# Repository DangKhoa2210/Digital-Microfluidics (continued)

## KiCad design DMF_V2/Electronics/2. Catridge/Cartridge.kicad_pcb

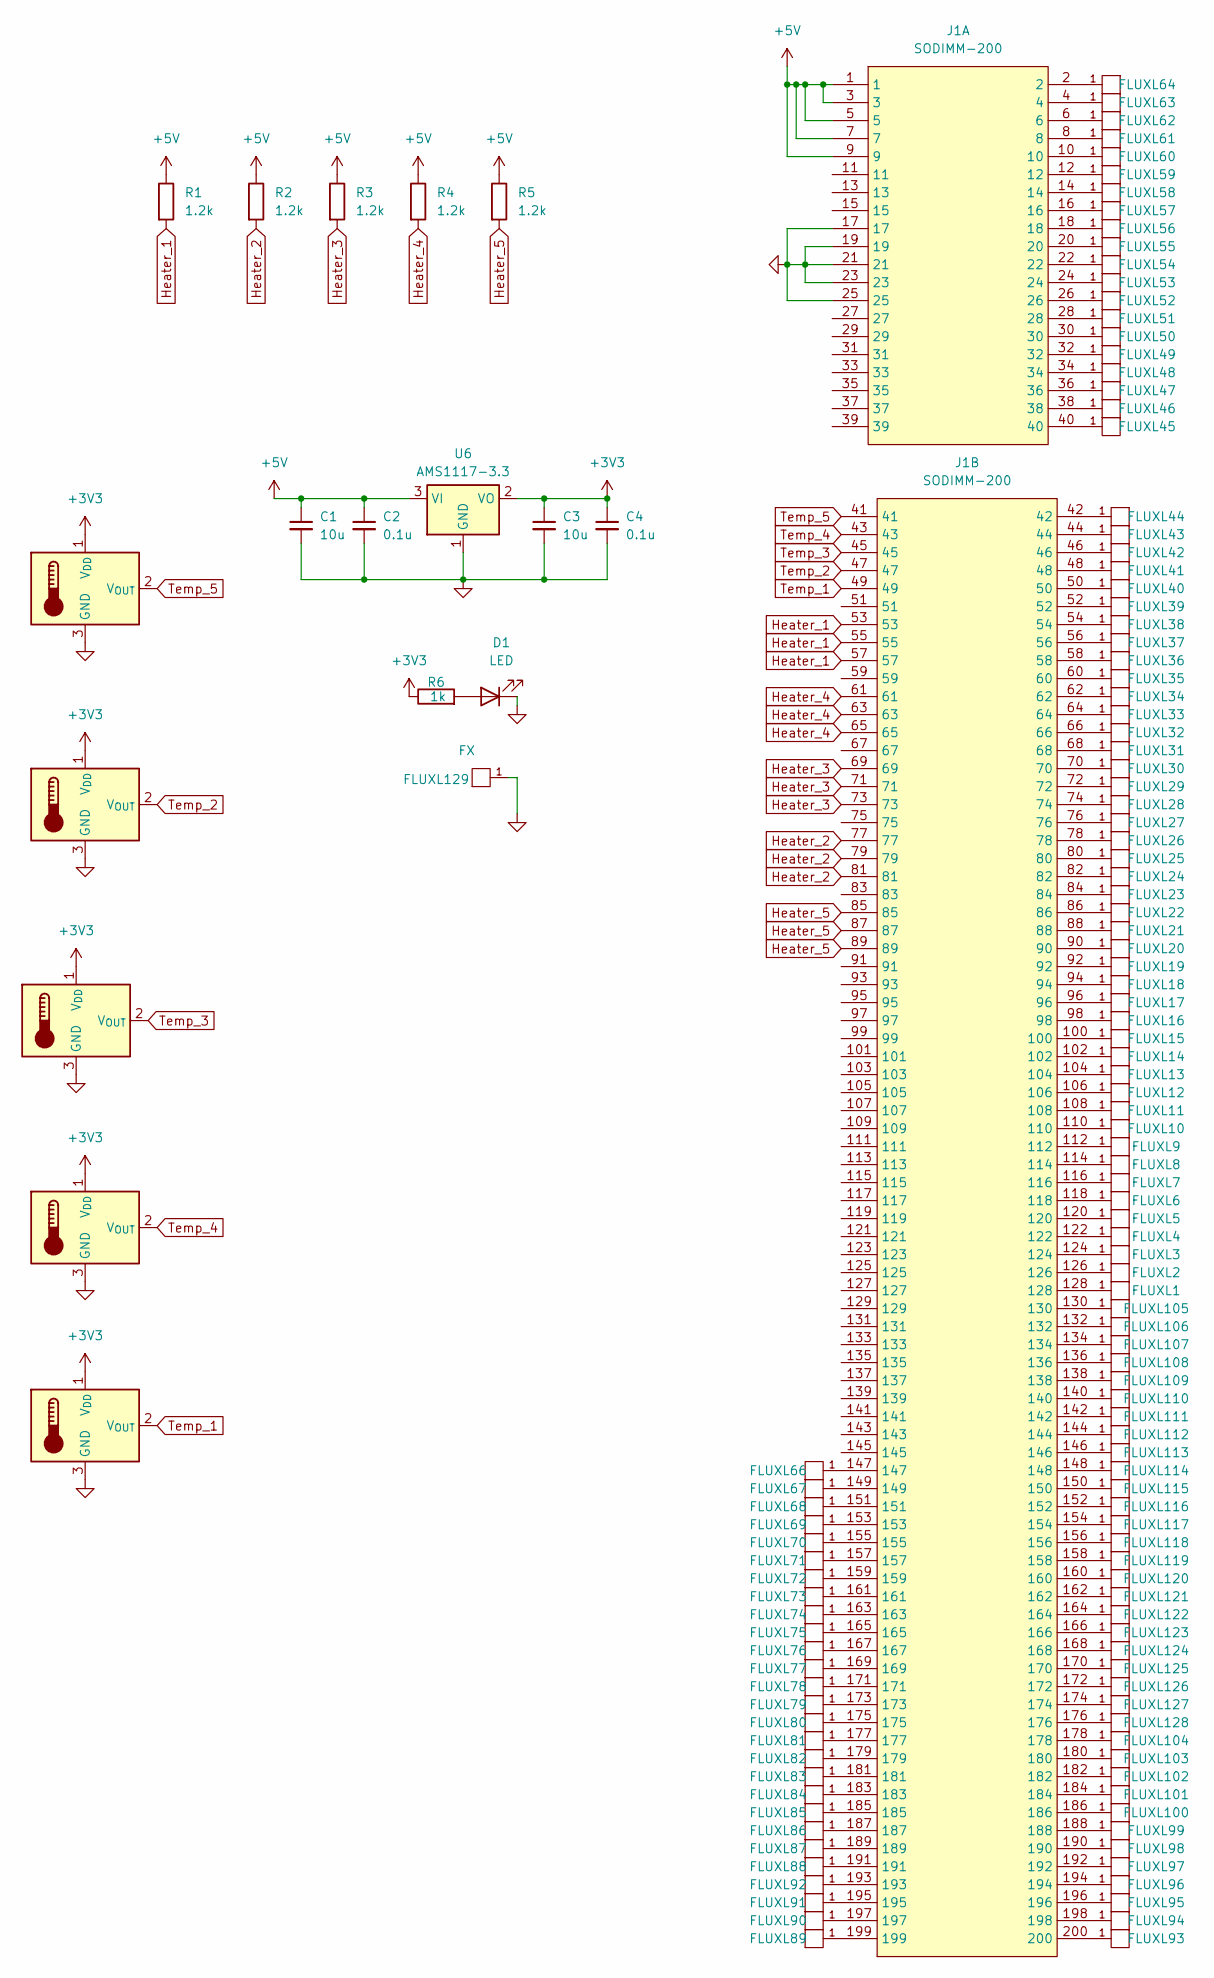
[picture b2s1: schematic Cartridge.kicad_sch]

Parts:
C1, C3: 10u; C_0402_1005Metric
C2, C4: 0.1u; C_0402_1005Metric
D1: LED; LED_0603_1608Metric
FLUXL1, FLUXL2, FLUXL3, FLUXL4, FLUXL5, FLUXL6, FLUXL7, FLUXL8, FLUXL9, FLUXL10, FLUXL11, FLUXL12, FLUXL13, FLUXL14, FLUXL15, FLUXL16, FLUXL17, FLUXL18, FLUXL19, FLUXL20, FLUXL21, FLUXL22, FLUXL23, FLUXL24, FLUXL25, FLUXL26, FLUXL27, FLUXL28, FLUXL29, FLUXL30, FLUXL31, FLUXL32, FLUXL33, FLUXL34, FLUXL35, FLUXL36, FLUXL37, FLUXL38, FLUXL39, FLUXL40, FLUXL41, FLUXL42, FLUXL43, FLUXL44, FLUXL45, FLUXL46, FLUXL47, FLUXL48, FLUXL49, FLUXL50, FLUXL51, FLUXL52, FLUXL53, FLUXL54, FLUXL55, FLUXL56, FLUXL57, FLUXL58, FLUXL59, FLUXL60, FLUXL61, FLUXL66, FLUXL67, FLUXL68, FLUXL69, FLUXL70, FLUXL71, FLUXL72, FLUXL73, FLUXL74, FLUXL75, FLUXL76, FLUXL77, FLUXL78, FLUXL79, FLUXL80, FLUXL81, FLUXL82, FLUXL83, FLUXL84, FLUXL85, FLUXL86, FLUXL87, FLUXL88, FLUXL89, FLUXL90, FLUXL91, FLUXL92, FLUXL93, FLUXL94, FLUXL95, FLUXL96, FLUXL97, FLUXL98, FLUXL99, FLUXL100, FLUXL101, FLUXL102, FLUXL103, FLUXL104, FLUXL105, FLUXL106, FLUXL107, FLUXL108, FLUXL109, FLUXL110, FLUXL111, FLUXL112, FLUXL113, FLUXL114, FLUXL115, FLUXL116, FLUXL117, FLUXL118, FLUXL119, FLUXL120, FLUXL121, FLUXL122, FLUXL123, FLUXL124, FLUXL125, FLUXL126, FLUXL127, FLUXL128: FX; FLUXPAD_2_75_4MIL_4_5
FLUXL62: FX; FLUXPAD_2_75_4MIL_4_5_res1
FLUXL63: FX; FLUXPAD_2_75_4MIL_4_5_res2
FLUXL64: FX; FLUXPAD_2_75_4MIL_4_5_res3
FLUXL129: FX; Pad_4mm_10mm
J1: SODIMM-200; DDR2
R1, R2, R3, R4, R5: 1.2k; R_1206_3216Metric
R6: 1k; R_0402_1005Metric
U1, U2, U3, U4, U5: MCP9700Ax-ETT; SOT-23
U6: AMS1117-3.3; SOT-223-3_TabPin2

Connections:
+3V3: C3.1, C4.1, R6.1, U1.1 (V_{DD}), U2.1 (V_{DD}), U3.1 (V_{DD}), U4.1 (V_{DD}), U5.1 (V_{DD}), U6.2 (VO)
+5V: C1.1, C2.1, J1.1, J1.3, J1.5, J1.7, J1.9, R1.1, R2.1, R3.1, R4.1, R5.1, U6.3 (VI)
GND: C1.2, C2.2, C3.2, C4.2, D1.1 (K), FLUXL129.1, J1.17, J1.19, J1.21, J1.23, J1.25, U1.3 (GND), U2.3 (GND), U3.3 (GND), U4.3 (GND), U5.3 (GND), U6.1 (GND)
Heater_1: J1.53, J1.55, J1.57, R1.2
Heater_2: J1.77, J1.79, J1.81, R2.2
Heater_3: J1.69, J1.71, J1.73, R3.2
Heater_4: J1.61, J1.63, J1.65, R4.2
Heater_5: J1.85, J1.87, J1.89, R5.2
unnamed: D1.2 (A), R6.2
unnamed: FLUXL1.1, J1.128
unnamed: FLUXL2.1, J1.126
unnamed: FLUXL3.1, J1.124
unnamed: FLUXL4.1, J1.122
unnamed: FLUXL5.1, J1.120
unnamed: FLUXL6.1, J1.118
unnamed: FLUXL7.1, J1.116
unnamed: FLUXL8.1, J1.114
unnamed: FLUXL9.1, J1.112
unnamed: FLUXL10.1, J1.110
unnamed: FLUXL11.1, J1.108
unnamed: FLUXL12.1, J1.106
unnamed: FLUXL13.1, J1.104
unnamed: FLUXL14.1, J1.102
unnamed: FLUXL15.1, J1.100
unnamed: FLUXL16.1, J1.98
unnamed: FLUXL17.1, J1.96
unnamed: FLUXL18.1, J1.94
unnamed: FLUXL19.1, J1.92
unnamed: FLUXL20.1, J1.90
unnamed: FLUXL21.1, J1.88
unnamed: FLUXL22.1, J1.86
unnamed: FLUXL23.1, J1.84
unnamed: FLUXL24.1, J1.82
unnamed: FLUXL25.1, J1.80
unnamed: FLUXL26.1, J1.78
unnamed: FLUXL27.1, J1.76
unnamed: FLUXL28.1, J1.74
unnamed: FLUXL29.1, J1.72
unnamed: FLUXL30.1, J1.70
unnamed: FLUXL31.1, J1.68
unnamed: FLUXL32.1, J1.66
unnamed: FLUXL33.1, J1.64
unnamed: FLUXL34.1, J1.62
unnamed: FLUXL35.1, J1.60
unnamed: FLUXL36.1, J1.58
unnamed: FLUXL37.1, J1.56
unnamed: FLUXL38.1, J1.54
unnamed: FLUXL39.1, J1.52
unnamed: FLUXL40.1, J1.50
unnamed: FLUXL41.1, J1.48
unnamed: FLUXL42.1, J1.46
unnamed: FLUXL43.1, J1.44
unnamed: FLUXL44.1, J1.42
unnamed: FLUXL45.1, J1.40
unnamed: FLUXL46.1, J1.38
unnamed: FLUXL47.1, J1.36
unnamed: FLUXL48.1, J1.34
unnamed: FLUXL49.1, J1.32
unnamed: FLUXL50.1, J1.30
unnamed: FLUXL51.1, J1.28
unnamed: FLUXL52.1, J1.26
unnamed: FLUXL53.1, J1.24
unnamed: FLUXL54.1, J1.22
unnamed: FLUXL55.1, J1.20
unnamed: FLUXL56.1, J1.18
unnamed: FLUXL57.1, J1.16
unnamed: FLUXL58.1, J1.14
unnamed: FLUXL59.1, J1.12
unnamed: FLUXL60.1, J1.10
unnamed: FLUXL61.1, J1.8
unnamed: FLUXL62.1, J1.6
unnamed: FLUXL63.1, J1.4
unnamed: FLUXL64.1, J1.2
unnamed: FLUXL66.1, J1.147
unnamed: FLUXL67.1, J1.149
unnamed: FLUXL68.1, J1.151
unnamed: FLUXL69.1, J1.153
unnamed: FLUXL70.1, J1.155
unnamed: FLUXL71.1, J1.157
unnamed: FLUXL72.1, J1.159
unnamed: FLUXL73.1, J1.161
unnamed: FLUXL74.1, J1.163
unnamed: FLUXL75.1, J1.165
unnamed: FLUXL76.1, J1.167
unnamed: FLUXL77.1, J1.169
unnamed: FLUXL78.1, J1.171
unnamed: FLUXL79.1, J1.173
unnamed: FLUXL80.1, J1.175
unnamed: FLUXL81.1, J1.177
unnamed: FLUXL82.1, J1.179
unnamed: FLUXL83.1, J1.181
unnamed: FLUXL84.1, J1.183
unnamed: FLUXL85.1, J1.185
unnamed: FLUXL86.1, J1.187
unnamed: FLUXL87.1, J1.189
unnamed: FLUXL88.1, J1.191
unnamed: FLUXL89.1, J1.199
unnamed: FLUXL90.1, J1.197
unnamed: FLUXL91.1, J1.195
unnamed: FLUXL92.1, J1.193
unnamed: FLUXL93.1, J1.200
unnamed: FLUXL94.1, J1.198
unnamed: FLUXL95.1, J1.196
unnamed: FLUXL96.1, J1.194
unnamed: FLUXL97.1, J1.192
unnamed: FLUXL98.1, J1.190
unnamed: FLUXL99.1, J1.188
unnamed: FLUXL100.1, J1.186
unnamed: FLUXL101.1, J1.184
unnamed: FLUXL102.1, J1.182
unnamed: FLUXL103.1, J1.180
unnamed: FLUXL104.1, J1.178
unnamed: FLUXL105.1, J1.130
unnamed: FLUXL106.1, J1.132
unnamed: FLUXL107.1, J1.134
unnamed: FLUXL108.1, J1.136
unnamed: FLUXL109.1, J1.138
unnamed: FLUXL110.1, J1.140
unnamed: FLUXL111.1, J1.142
unnamed: FLUXL112.1, J1.144
unnamed: FLUXL113.1, J1.146
unnamed: FLUXL114.1, J1.148
unnamed: FLUXL115.1, J1.150
unnamed: FLUXL116.1, J1.152
unnamed: FLUXL117.1, J1.154
unnamed: FLUXL118.1, J1.156
unnamed: FLUXL119.1, J1.158
unnamed: FLUXL120.1, J1.160
unnamed: FLUXL121.1, J1.162
unnamed: FLUXL122.1, J1.164
unnamed: FLUXL123.1, J1.166
unnamed: FLUXL124.1, J1.168
unnamed: FLUXL125.1, J1.170
unnamed: FLUXL126.1, J1.172
unnamed: FLUXL127.1, J1.174
unnamed: FLUXL128.1, J1.176
Temp_1: J1.49, U5.2 (V_{OUT})
Temp_2: J1.47, U2.2 (V_{OUT})
Temp_3: J1.45, U3.2 (V_{OUT})
Temp_4: J1.43, U4.2 (V_{OUT})
Temp_5: J1.41, U1.2 (V_{OUT})

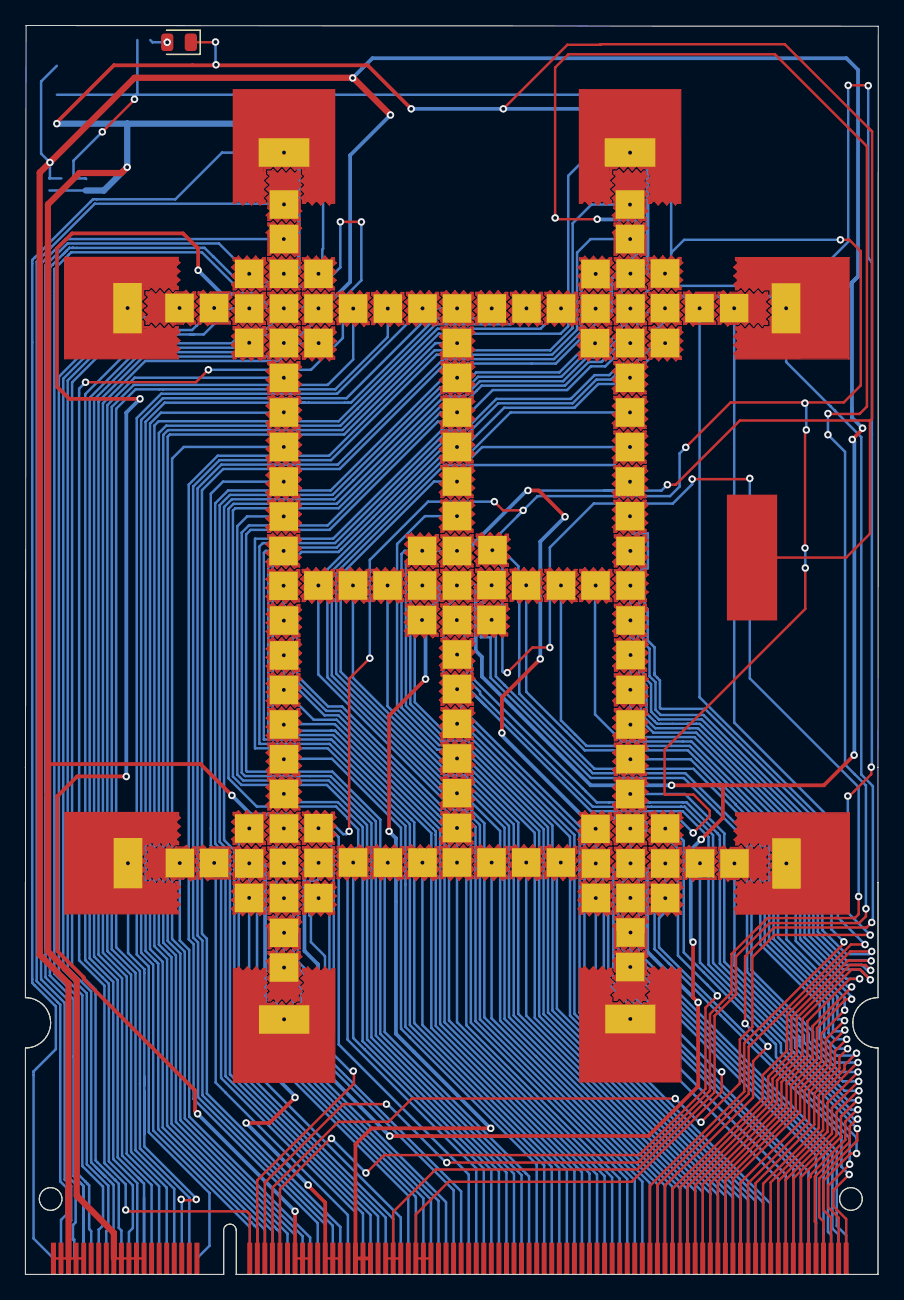
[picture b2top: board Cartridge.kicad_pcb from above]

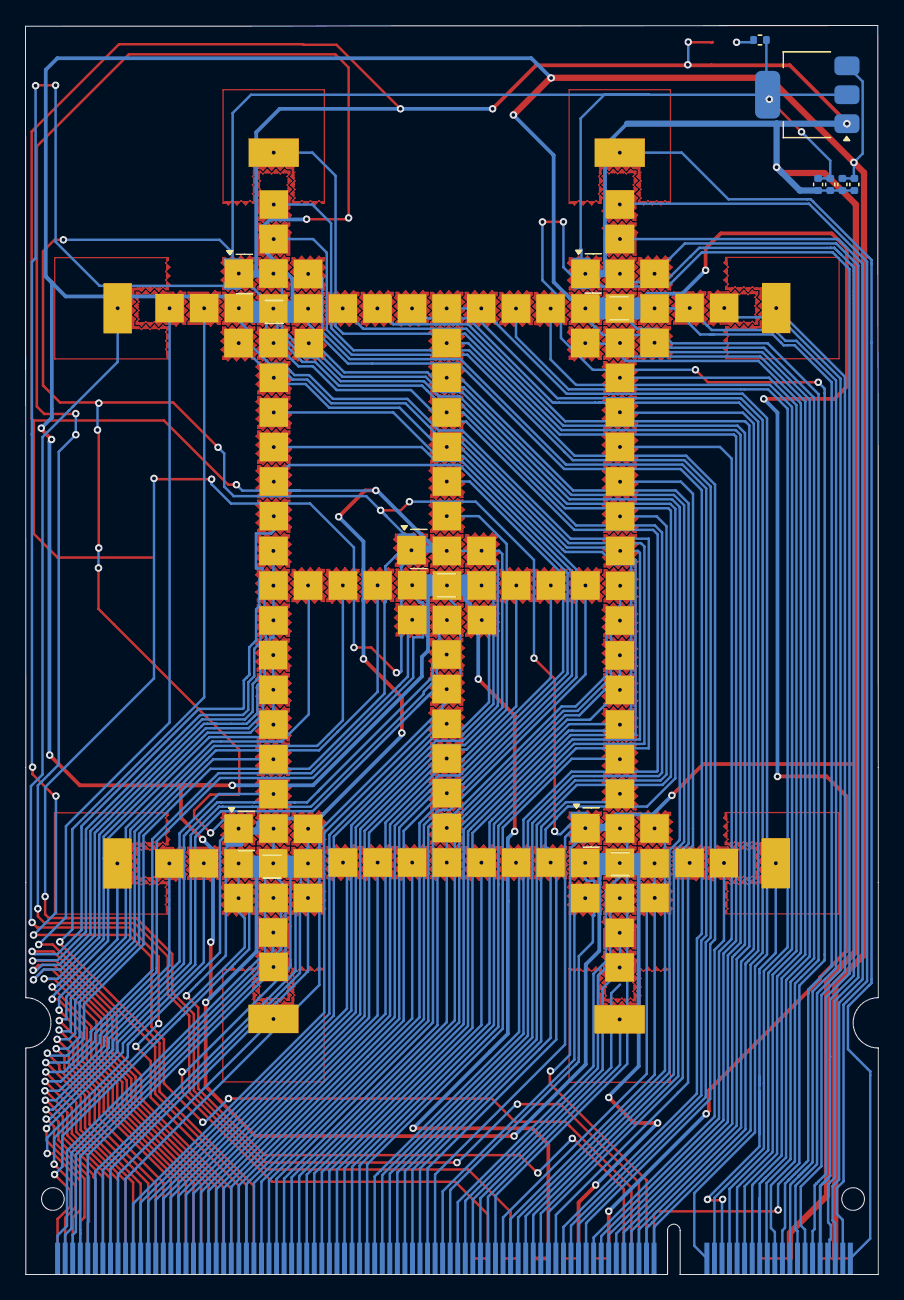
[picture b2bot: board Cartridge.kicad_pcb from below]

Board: 2 copper layers, 67.8 x 99.3 mm, 146 parts (16 on the bottom side), 141 nets.

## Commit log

2025-07-13 Cartridege_V2
